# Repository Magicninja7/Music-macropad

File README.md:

Description: A macropad, especially created for music control. it has a pause, forward, and backward for songs, knob for volume, and 2 other customizable buttons!
Why? I am annnoyed that i have to change pages (when a horrible song plays), to go to the tab i have yt music on. It would be easier, if i had a dedicated thing to control all of that, without the need to quit my task.

## CAD:

## PCB:

## Schematic:

| item | price | quantity | total | link |
| ---- | ----- | -------- | ----- | ---- |
| Cherry mx switch | 1$ | 10 | 1$ | https://pl.aliexpress.com/item/1005007474127225.html?aem_p4p_detail=202507030451029315849861737520001746820&algo_pvid=e89e75e1-1e78-4e5f-be1d-b30f5ad94cdb&algo_exp_id=e89e75e1-1e78-4e5f-be1d-b30f5ad94cdb-0&pdp_ext_f=%7B%22order%22%3A%2275%22%2C%22eval%22%3A%221%22%7D&pdp_npi=4%40dis%21PLN%2122.98%2115.33%21%21%2144.43%2129.63%21%40211b819117515434628977966ea375%2112000040899468611%21sea%21PL%210%21ABX&curPageLogUid=rRNwJJ2Rphf3&utparam-url=scene%3Asearch%7Cquery_from%3A&search_p4p_id=202507030451029315849861737520001746820_1 |
| keycaps | - | 5 | - | - |
| raspi pico | - | 1 | - | - |
| Case | - | 1 | - | (my own 3d printer) |
| pcb | 4$ | 1 | 4$ | https://cart.jlcpcb.com/shopcart/cart/ |

total: 5$ (no customs! and low shipping)

Note: the places where i placed -, means i already have that part so i don't need to purchase it

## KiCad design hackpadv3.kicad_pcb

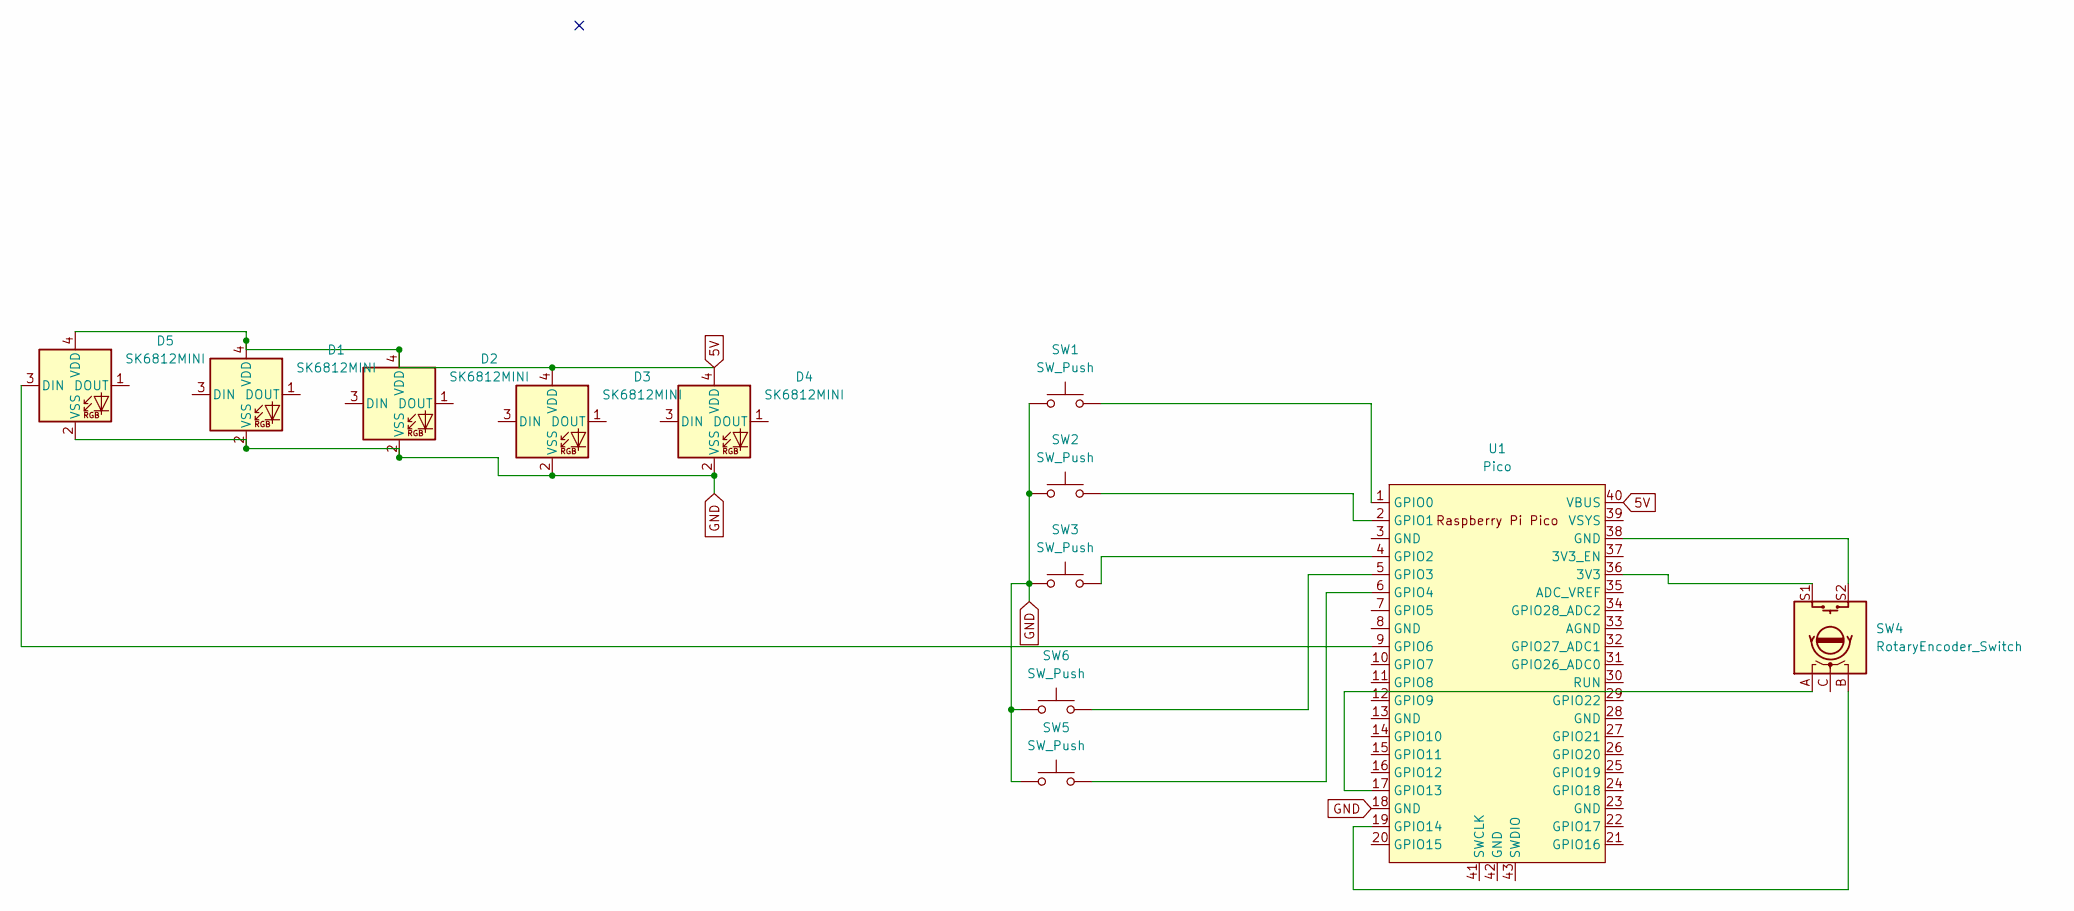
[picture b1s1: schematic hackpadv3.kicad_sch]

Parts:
D1, D2, D3, D4, D5: SK6812MINI; LED_SK6812MINI_PLCC4_3.5x3.5mm_P1.75mm
SW1, SW2, SW3, SW5, SW6: SW_Push; SW_Cherry_MX_1.00u_PCB
SW4: RotaryEncoder_Switch; RotaryEncoder_Alps_EC11E-Switch_Vertical_H20mm
U1: Pico; RPi_Pico_SMD_TH

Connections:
5V: D1.4 (VDD), D2.4 (VDD), D3.4 (VDD), D4.4 (VDD), D5.4 (VDD), U1.40 (VBUS)
GND: D1.2 (VSS), D2.2 (VSS), D3.2 (VSS), D4.2 (VSS), D5.2 (VSS), SW1.1, SW2.1, SW3.1, SW5.1, SW6.1, U1.18 (GND)
unnamed: D5.3 (DIN), U1.9 (GPIO6)
unnamed: SW4.S2, U1.38 (GND)
unnamed: SW4.S1, U1.36 (3V3)
unnamed: SW1.2, U1.1 (GPIO0)
unnamed: SW2.2, U1.2 (GPIO1)
unnamed: SW3.2, U1.4 (GPIO2)
unnamed: SW6.2, U1.5 (GPIO3)
unnamed: SW5.2, U1.6 (GPIO4)
unnamed: SW4.A, U1.17 (GPIO13)
unnamed: SW4.B, U1.19 (GPIO14)

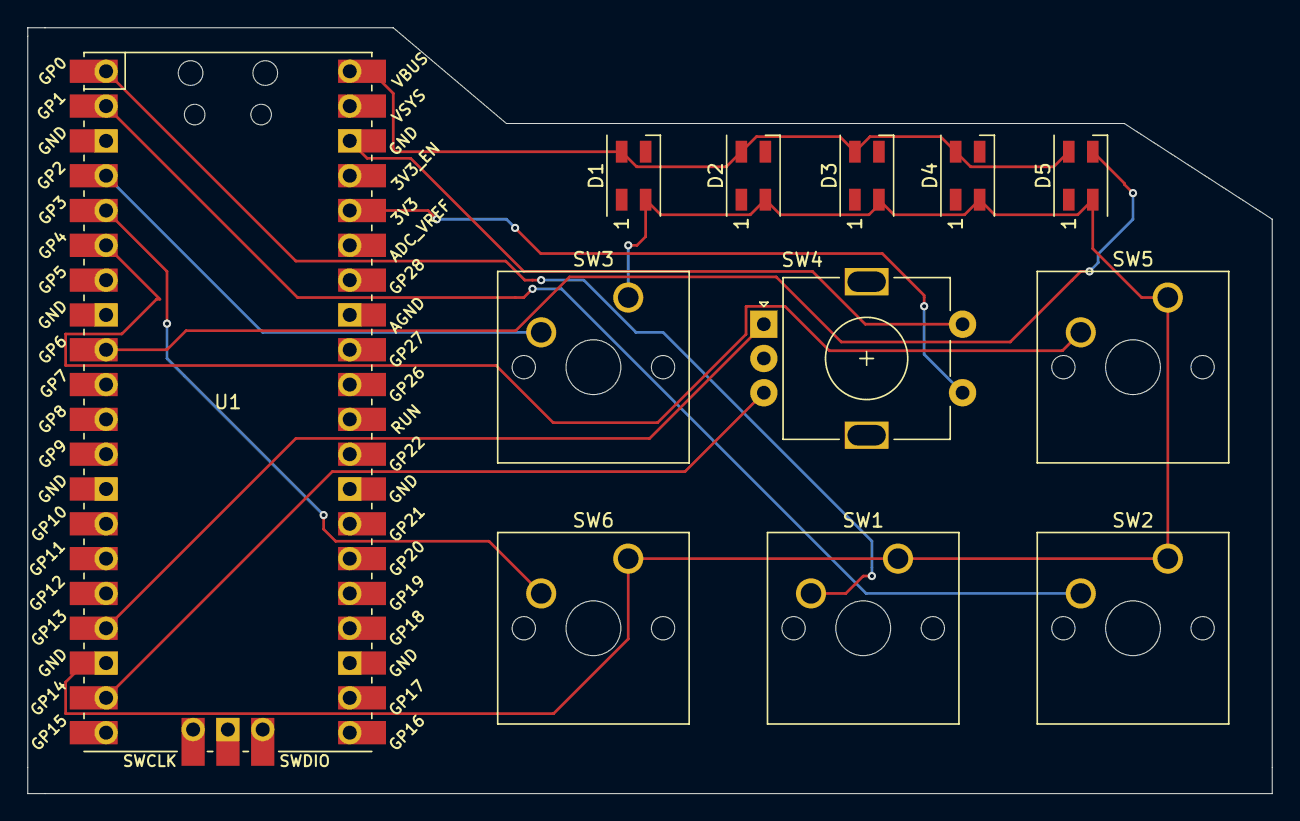
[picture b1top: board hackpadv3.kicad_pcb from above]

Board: 2 copper layers, 90.8 x 55.9 mm, 12 parts (0 on the bottom side), 12 nets.

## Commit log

2025-07-03 Rename hackpadv3.kicad_prl to PCB/hackpadv3.kicad_prl
2025-07-03 Rename hackpadv3.kicad_pro to PCB/hackpadv3.kicad_pro
2025-07-03 Update and rename sym-lib-table to PCB/sym-lib-table
2025-07-04 Rename gerbershackpad.zip to production/gerbershackpad.zip
